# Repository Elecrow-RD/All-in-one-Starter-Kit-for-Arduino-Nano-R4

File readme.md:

## Menu
### 1, Product picture
### 2, Product version number
### 3, product information
### 4, Use the driver module
### 5,Quick Start
### 6,Folder structure.
### 7,Pin definition

### 1, Product picture

#### 2, Product version number

|      | Hardware | Software | Remark |
| ---- | -------- | -------- | ------ |
| 1    | V1.0     | V1.0     | latest |

### 3, product information

| Main Processor        | Arduino NANO R4                                        |
| --------------------- | ------------------------------------------------------ |
| CPU/SoC               | RA4M1(Arm® Cortex-M4®)                                 |
| System memory         | RAM32KB                                                |
| Storage               | Flash 256 kB                                           |
| Bluetooth             | None                                                   |
| WiFi                  | None                                                   |
| Interface             | TYPE-C interface, I/O pins/sockets, Crowtail interface |
| Button                | Reset                                                  |
| LED indicator light   | Reset indicator light, power indicator light           |
| Power input           | 5V input charging                                      |
| Shell material        | PP (non-toxic)                                         |
| Size                  | 195\*170*46（mm）                                      |
| Net Weight            | 415g                                                      |
| Operating temperature | 0°C to 60°C                                            |
| Storage temperature   | 0°C to 60°C                                            |

### 4, Use the driver module

| Name     | dependency library                           |
| -------- | -------------------------------------------- |
| IRremote | Arduino-IRremote-master <br />version: 4.5.0 |
| LSM6DS3  | Arduino_LSM6DS3-master<br />version=1.0.3    |
| BH1750   | BH1750<br />version: 1.3.0                   |

### 5,Quick Start
### Arduino IDE starts

1.Download the library files used by this product to the 'libraries' folder.

C:\Users\Documents\Arduino\libraries\

2.Install the NANO R4 development board and open the program files

3.Open the code configuration environment and burn it

### 6,Folder structure.

|--Eagle_SCH&PCB: Contains **Eagle CAD** schematic (`.sch`) and PCB layout (`.brd`) files. These are used for circuit design and PCB manufacturing.

|--lesson_code: Provides  code and projects to demonstrate how to use the hardware and libraries. These examples help users get started quickly.

|--libraries: Includes necessary libraries required for compiling and running the project. These libraries provide drivers and additional functionalities for the hardware.

### 7,Pin definition

#### Sensor / Module List

| No.  | Sensor / Module Name          | Quantity | Notes                            | nano pin                                                     |
| ---- | ----------------------------- | -------- | -------------------------------- | ------------------------------------------------------------ |
| 1    | Temperature & Humidity Sensor | 1        |                                  | A4/SDA<br />A5/SCL<br />I2C  ADDRESS:0X38                    |
| 2    | Button                        | 3        |                                  | A3_KEY                                                       |
| 3    | Ultrasonic Ranging Sensor     | 1        |                                  | D7_US_ECHO<br />D6_US_TRIG                                   |
| 4    | Light Sensor                  | 1        |                                  | A4/SDA<br />A5/SCL<br />I2C  ADDRESS:0X5C                    |
| 5    | Linear Potentiometer          | 1        |                                  | A0_ROTARY                                                    |
| 6    | LED (Red + Yellow + Green)    | 3        | Red + Yellow + Green             | ~D5_LED_R<br />~D10_LED_Y<br />~D11_LED_G                    |
| 7    | Buzzer                        | 1        |                                  | D3_BUZZER                                                    |
| 8    | LCD Display                   | 1        |                                  | A4/SDA<br />A5/SCL<br />I2C  ADDRESS:0X27                    |
| 9    | Infrared Remote               | 1        | Includes remote controller       | D2_IR_R                                                      |
| 10   | Relay Module                  | 1        |                                  | D4_RELAY                                                     |
| 11   | Servo Motor                   | 1        |                                  | D9_SERVO                                                     |
| 12   | Sound Sensor                  | 1        |                                  | A1_SOUND                                                     |
| 13   | 3-Axis Accelerometer          | 1        |                                  | A4/SDA<br />A5/SCL<br />I2C  ADDRESS:0x6B (pin SDO is logic High) |
| 14   | PIR Motion Sensor             | 1        |                                  | A2_PIR                                                       |
| 15   | Soil Moisture Sensor          | 1        | Separate probe, 4-wire connector | A7                                                           |
| 16   | 4-Digit Display               | 1        |                                  | A4/SDA<br />A5/SCL<br />I2C  ADDRESS:0X70                    |

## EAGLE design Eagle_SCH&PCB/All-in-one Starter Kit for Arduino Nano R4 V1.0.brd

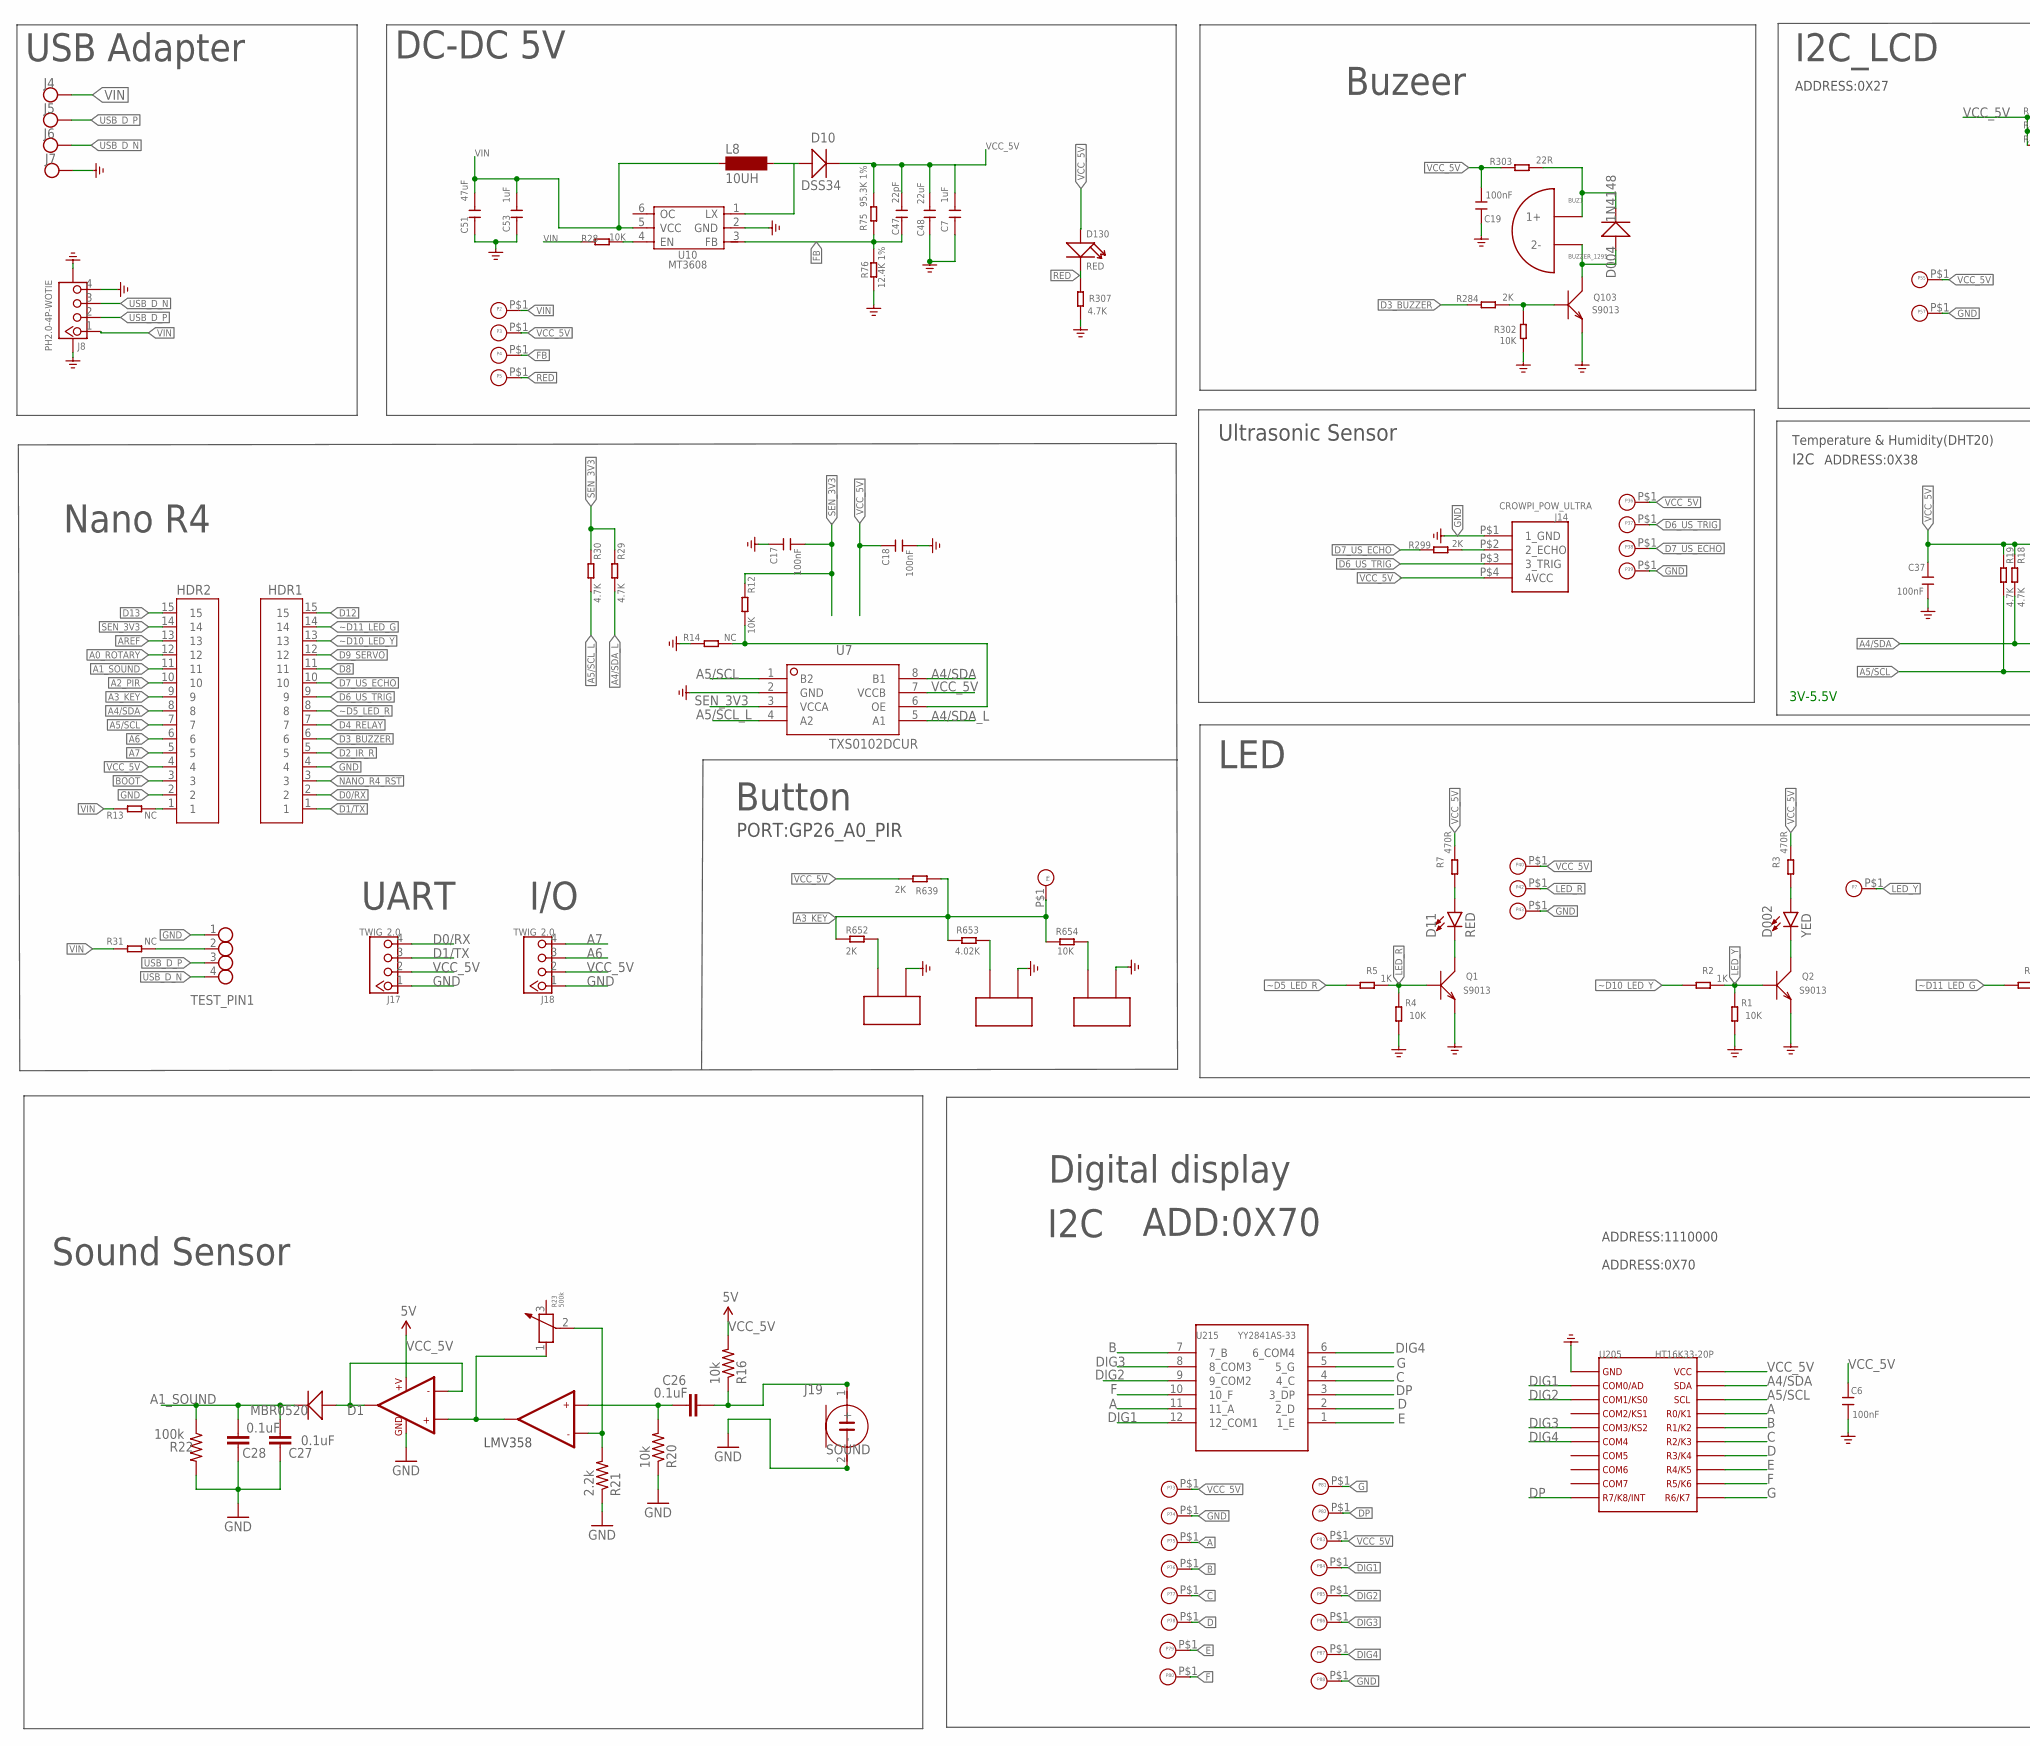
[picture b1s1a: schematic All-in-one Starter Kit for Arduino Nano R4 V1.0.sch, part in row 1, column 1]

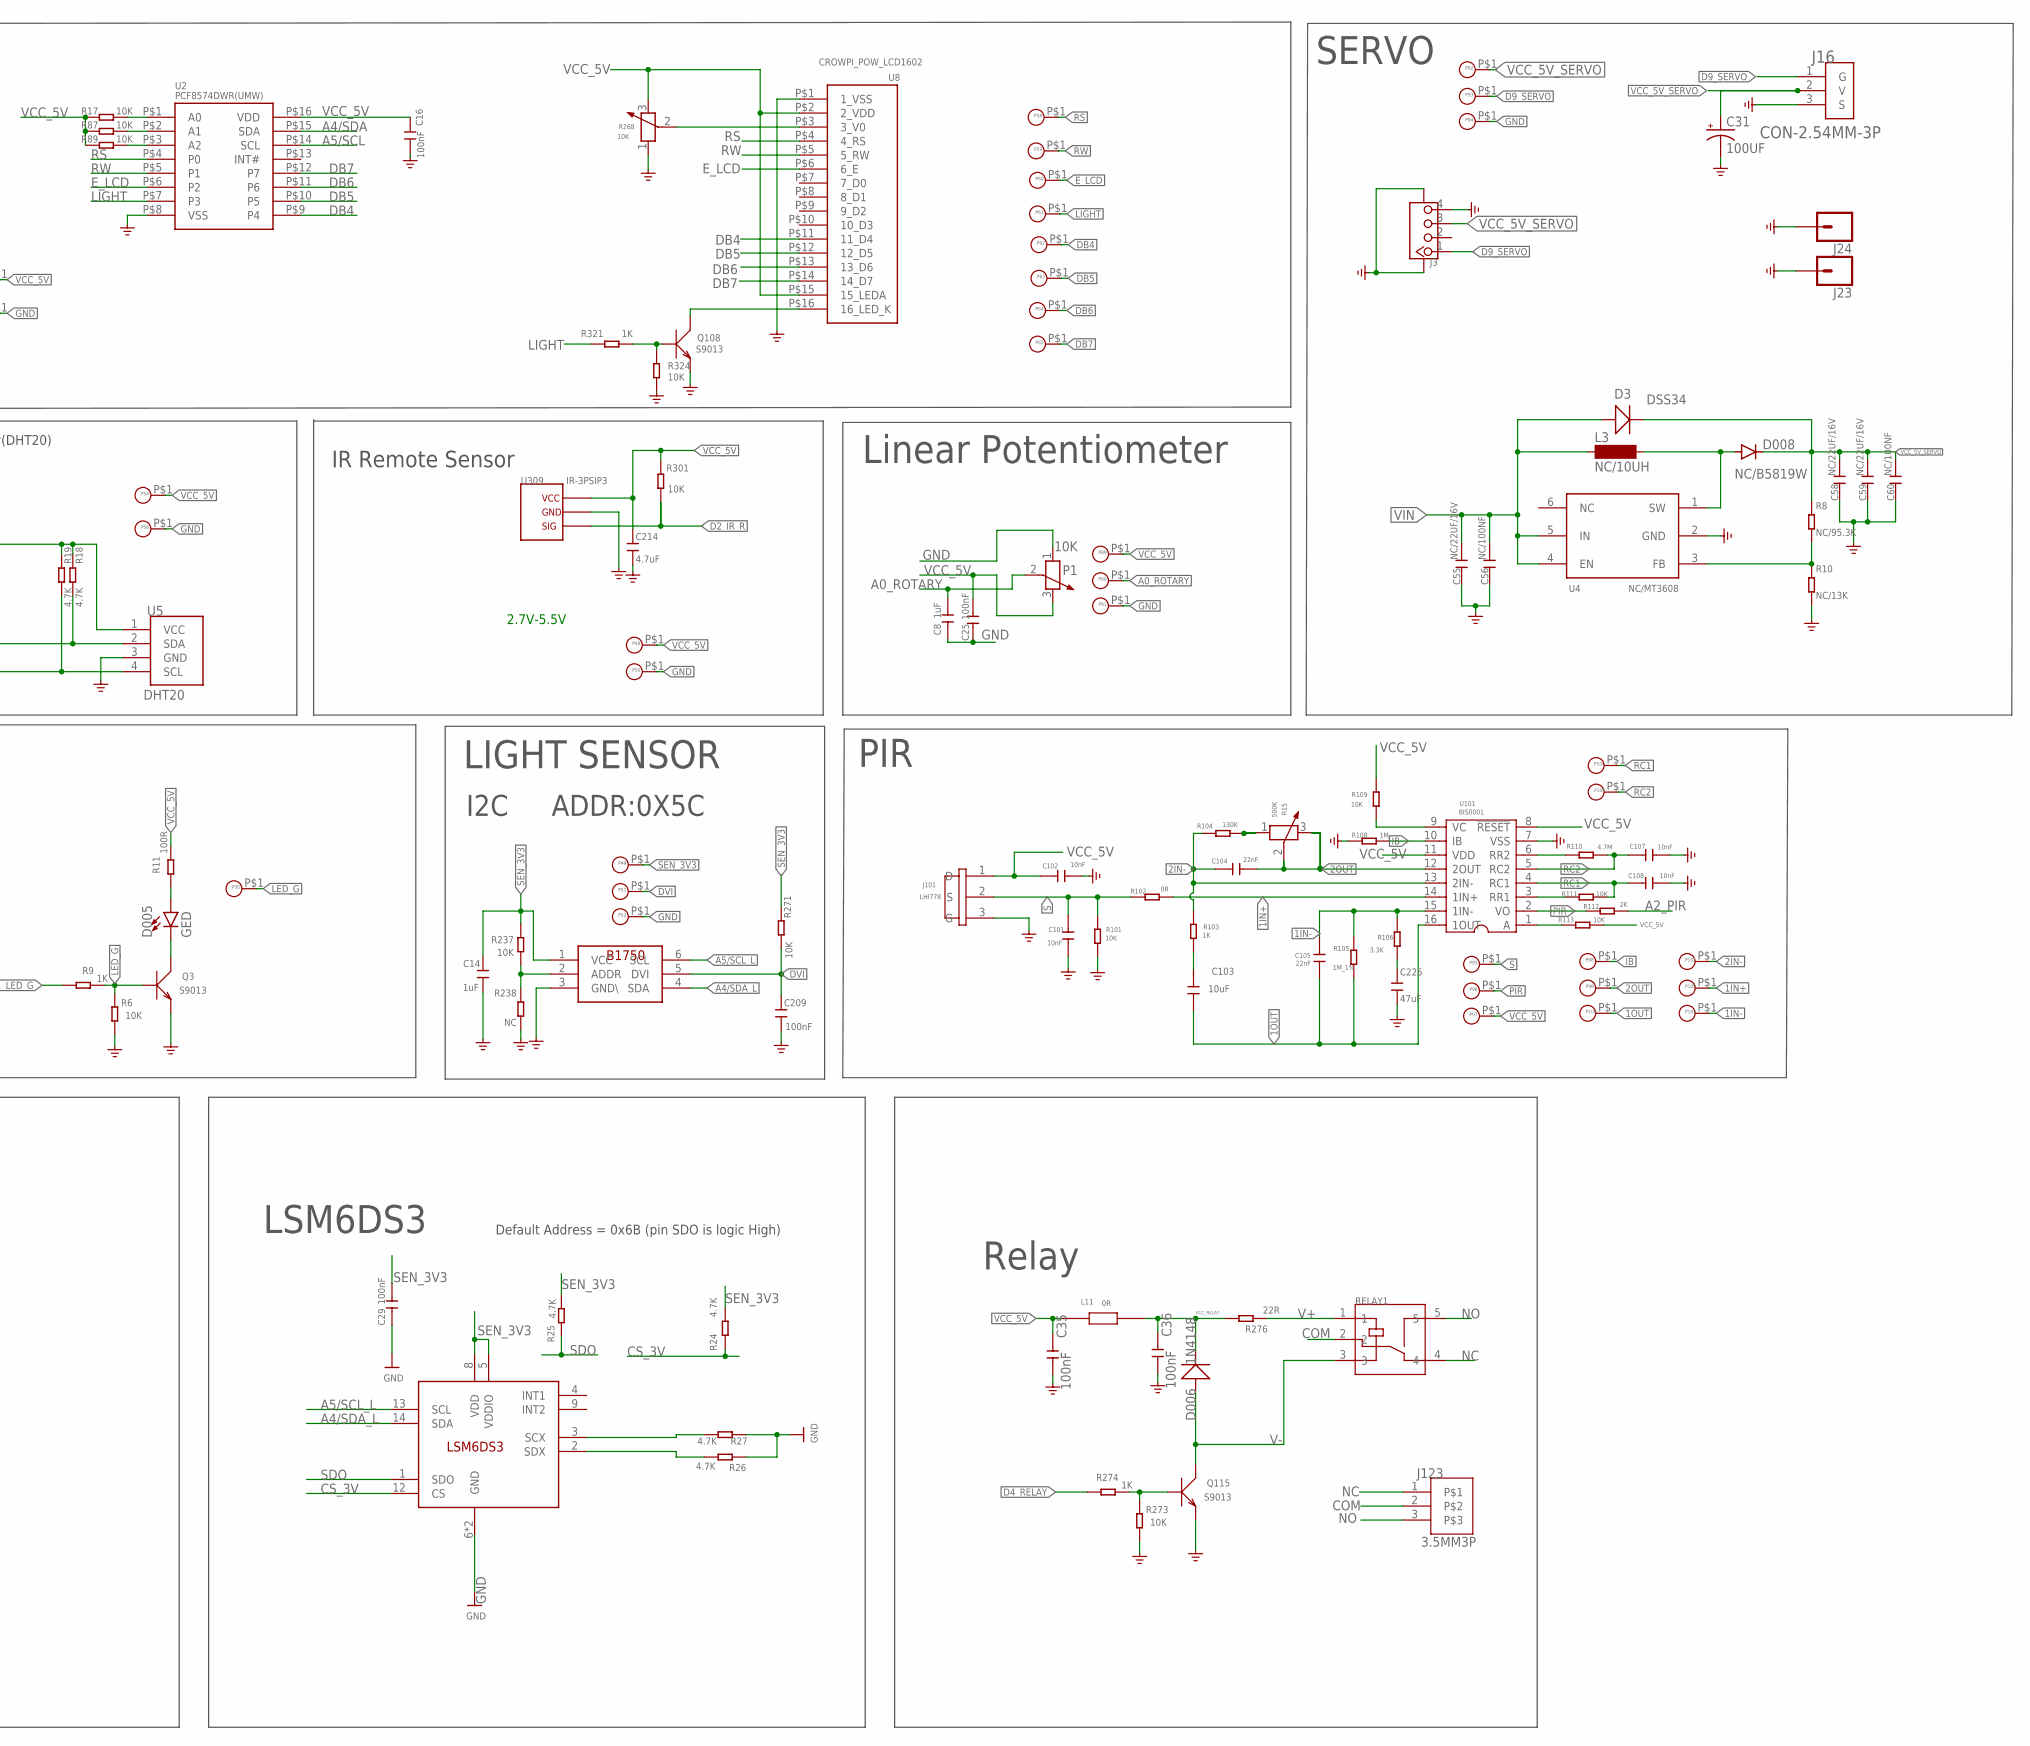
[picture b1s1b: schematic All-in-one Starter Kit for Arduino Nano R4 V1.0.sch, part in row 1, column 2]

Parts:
BUZ1: BUZZER_1295; BUZZER-D12MM-DIP2
C6, C16, C17, C18, C19, C37, C209: 100nF; 0603
C7, C8, C53: 1uF; C0603
C14: 1uF; 0603
C25, C29, C35, C36: 100nF; C0603
C26, C27, C28: 0.1uF; 0603-CAP
C31: 100UF; SANYO-OSCON_SMD_C6
C47: 22pF; C0603
C48: 22uF; C0805
C51: 47uF; C0805
C55, C58, C59: NC/22UF/16V; C0603
C56, C60: NC/100NF; C0603
C101, C102, C107, C108: 10nF; C0603
C103: 10uF; 0603
C104, C105: 22nF; C0603
C214: 4.7uF; 0603
C225: 47uF; 0805
D1: MBR0520; SOD123-2.7X1.6
D002: YED; LED-8MM
D3, D10: DSS34; D_SOD123FL
D004, D006: 1N4148; D_SOD123
D005: GED; LED-8MM
D008: NC/B5819W; SOD-123_MINI-SMA
D11: RED; LED-8MM
D130: RED; LED_0603_SMT
HDR1, HDR2: KH-2.54FH-1X15P-H8.5; HDR-TH_15P-P2.54-V-F
J3: A_XBJ_CONNECTOR_TWIG-4P-2.0-SMD-FEMALE-REINFORCE9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; A_XBJ_CONNECTOR_4P-SMD-2.0-90D
J4, J5, J6, J7: TP-SMDTP-SMD-2X4MM; TP-SMD-2X4MM
J8: PH2.0-4P-WOTIE; PH2.0-4P
J14: CROWPI_POW_ULTRA
J16: CON-2.54MM-3P; CON-PZ-2.54MM-1*3P-WT
J17, J18: TWIG_2.0; 2.0_1X4
J19: SOUND; TEMPLATE_2P-D8.9MM
J23, J24: CONN_01_2.6MM1X01_2.6-4MM; 1X01_2.6MM
J101: LHI778; 3P-D8.1MM
J123: 3.5MM3P; 3.5MM*3P
K1, K2, K3: BUTTON_2P
L3: NC/10UH; MS42
L8: 10UH; MS42
L11: 0R; 201209
P1: 10K; 3P-SQUA-45.6X10X5.8H
P2, P3, P4, P5, P6, P7, P30, P36, P37, P38, P39, P40, P42, P43, P48, P49, P50, P51, P52, P54, P55, P56, P57, P58, P59, P60, P61, P62, P63, P64, P65, P73, P74, P75, P76, P77, P78, P79, P80, P81, P82, P83, P84, P85, P86, P87, P88, P89, P90, P91, P92, P93, P94, P95, P96, P97, P98, P99, P100, P101, P102, P103, P104, P105: PADPAD-1.0MM; PAD-1.0MM
Q1, Q2, Q3, Q103, Q108, Q115: S9013; SOT23@1
R1, R4, R6, R12, R17, R87, R89, R101, R109, R111, R113, R237, R271, R273, R301, R302, R324, R654: 10K; R0603
R2, R5, R9, R103, R274, R321: 1K; R0603
R3, R7: 470R; R0603
R8: NC/95.3K; R0603
R10: NC/13K; R0603
R11: 100R; R0603
R13, R14, R31, R238: NC; R0603
R15: 500K; 3P-SMD-SQUA-3.6X3.3
R16, R20: 10k; 0603-RES
R18, R19, R24, R25, R26, R27, R29, R30, R307: 4.7K; R0603
R21: 2.2k; 0603-RES
R22: 100k; 0603-RES
R23: 500k; 3P-SMD-SQUA-3.6X3.3
R28: 10K; R0603-SP
R75: 95.3K 1%; R0603-SP
R76: 12.4K 1%; R0603-SP
R102: 0R; R0603
R104: 130K; R0603
R105: 1M_1%; R0603
R106: 3.3K; R0603
R108: 1M; R0603
R110: 4.7M; R0603
R112, R284, R299, R639, R652: 2K; R0603
R268: 10K; 3P-SMD-SQUA-3.6X3.3
R276, R303: 22R; R0603
R653: 4.02K; R0603
RELAY1: RELAY-SRD; REY5-6-19.1X15.5X15.3MM
TEST_PIN1: POGOPIN_4
U1: BH1750; BH1750-WSOF-6
U2: PCF8574DWR(UMW); SO-16-300MIL
U3: LSM6DS3; LGA-14L
U4: NC/MT3608; DBV_R-PDSO-G6
U5: DHT20; CROWTAIL-DHT20-V1.0-20211013_DHT20
U6: LMV358; SO08
U7: TXS0102DCUR; VSSOP-8
U8: CROWPI_POW_LCD1602; CROWPI_POW_LCD1206
U10: MT3608; SOT23-6L
U101: BIS0001; SOP16
U205: HT16K33-20P; HT16K33-SOP20
U215: YY2841AS-33; 4-DIGITAL_DISPLAY
U309: IR-3PSIP3; VS1838B-SIP3

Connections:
1IN+: P102.P$1, R102.1, U101.14 (1IN+)
1IN-: C105.2, P103.P$1, R105.2, R106.2, U101.15 (1IN-)
1OUT: C103.2, C105.1, P100.P$1, R105.1, U101.16 (1OUT)
2IN-: C104.1, P101.P$1, R103.2, R104.2, U101.13 (2IN-)
2OUT: C104.2, P99.P$1, R15.2 (3), R15.3 (2), U101.12 (2OUT)
A: P75.P$1, U205.P$17, U215.11 (11_A)
A0_ROTARY: C8.2, HDR2.12, P1.2 (3), P90.P$1
A1_SOUND: C27.2, C28.2, D1.2 (-), HDR2.11, R22.1
A2_PIR: HDR2.10, R112.1
A3_KEY: HDR2.9, P6.P$1, R639.2, R652.2, R653.2, R654.2
A4/SDA: HDR2.8, R18.2, U2.P$15 (SDA), U5.2 (SDA), U7.8 (B1), U205.P$19
A4/SDA_L: R29.2, U1.4 (SDA), U3.14 (SDA), U7.5 (A1)
A5/SCL: HDR2.7, R19.2, U2.P$14 (SCL), U5.4 (SCL), U7.1 (B2), U205.P$18
A5/SCL_L: R30.2, U1.6 (SCL), U3.13 (SCL), U7.4 (A2)
A6: HDR2.6, J18.3
A7: HDR2.5, J18.4
AREF: HDR2.13
B: P76.P$1, U205.P$16, U215.7 (7_B)
BOOT: HDR2.3
C: P77.P$1, U205.P$15, U215.4 (4_C)
COM: J123.2, RELAY1.2
CS_3V: R24.1, U3.12 (CS)
D: P78.P$1, U205.P$14, U215.2 (2_D)
D0/RX: HDR1.2, J17.4
D1/TX: HDR1.1, J17.3
D2_IR_R: HDR1.5, R301.2, U309.3
D3_BUZZER: HDR1.6, R284.1
D4_RELAY: HDR1.7, R274.2
D6_US_TRIG: HDR1.9, J14.P$3 (3_TRIG), P37.P$1
D7_US_ECHO: HDR1.10, P38.P$1, R299.2
D8: HDR1.11
D9_SERVO: HDR1.12, J3.1, J16.1 (G), P93.P$1
D12: HDR1.15
D13: HDR2.15
DB4: P62.P$1, U2.P$9 (P4), U8.P$11 (11_D4)
DB5: P63.P$1, U2.P$10 (P5), U8.P$12 (12_D5)
DB6: P64.P$1, U2.P$11 (P6), U8.P$13 (13_D6)
DB7: P65.P$1, U2.P$12 (P7), U8.P$14 (14_D7)
DIG1: P84.P$1, U205.P$2, U215.12 (12_COM1)
DIG2: P85.P$1, U205.P$3, U215.9 (9_COM2)
DIG3: P86.P$1, U205.P$5, U215.8 (8_COM3)
DIG4: P87.P$1, U205.P$6, U215.6 (6_COM4)
DP: P82.P$1, U205.P$10, U215.3 (3_DP)
DVI: C209.2, P51.P$1, R271.2, U1.5 (DVI)
E: P79.P$1, U205.P$13, U215.1 (1_E)
E_LCD: P60.P$1, U2.P$6 (P2), U8.P$6 (6_E)
F: P80.P$1, U205.P$12, U215.10 (10_F)
FB: C47.2, P4.P$1, R75.1, R76.2, U10.3 (FB)
G: P81.P$1, U205.P$11, U215.5 (5_G)
GND: C6.1, C7.1, C8.1, C14.1, C16.1, C17.2, C18.1, C19.2, C25.1, C27.1, C28.1, C29.1, C31.-, C35.1, C36.1, C37.1, C48.1, C51.1, C53.1, C55.1, C56.1, C58.1, C59.1, C60.1, C101.1, C102.1, C107.2, C108.2, C209.1, C214.1, C225.1, HDR1.4, HDR2.2, J3.4, J3.SS1, J3.SS2, J7.1, J8.4, J8.5 (SS1), J8.6 (SS2), J14.P$1 (1_GND), J16.3 (S), J17.1, J18.1, J19.2 (-), J23.1, J24.1, J101.3 (G), K1.P$1, K2.P$1, K3.P$1, P1.1, P39.P$1, P43.P$1, P50.P$1, P52.P$1, P56.P$1, P57.P$1, P74.P$1, P88.P$1, P91.P$1, P94.P$1, Q1.2 (E), Q2.2 (E), Q3.2 (E), Q103.2 (E), Q108.2 (E), Q115.2 (E), R1.1, R4.1, R6.1, R10.2, R14.1, R20.1, R21.1, R22.2, R26.1, R27.1, R76.1, R101.1, R108.1, R238.1, R268.1, R273.1, R302.1, R307.2, R324.2, TEST_PIN1.1, U1.3 (GND\), U2.P$8 (VSS), U3.6 (GND), U3.7 (GND), U4.2 (GND), U5.3 (GND), U6.4 (GND), U7.2 (GND), U8.P$1 (1_VSS), U10.2 (GND), U101.7 (VSS), U205.P$1, U309.2
IB: P98.P$1, R108.2, U101.10 (IB)
LED_G: P30.P$1, Q3.1 (B), R6.2, R9.1
LED_R: P42.P$1, Q1.1 (B), R4.2, R5.1
LED_Y: P7.P$1, Q2.1 (B), R1.2, R2.1
LIGHT: P61.P$1, R321.2, U2.P$7 (P3)
unnamed: R111.1, U101.3 (RR1)
unnamed: Q108.1 (B), R321.1, R324.1
unnamed: C225.2, R106.1
unnamed: D10.+, L8.2, U10.1 (LX)
unnamed: D002.2 (C), Q2.3 (C)
unnamed: R28.2, U10.4 (EN)
unnamed: R268.2 (3), U8.P$3 (3_V0)
unnamed: D002.1 (A), R3.2
unnamed: D005.2 (C), Q3.3 (C)
unnamed: R17.2, U2.P$1 (A0)
unnamed: R87.2, U2.P$2 (A1)
unnamed: R89.2, U2.P$3 (A2)
unnamed: D008.A, L3.2, U4.1 (SW)
unnamed: D005.1 (A), R11.2
unnamed: D11.2 (C), Q1.3 (C)
unnamed: D11.1 (A), R7.2
unnamed: R31.1, TEST_PIN1.2
unnamed: HDR2.1, R13.1
unnamed: Q108.3 (C), U8.P$16 (16_LED_K)
unnamed: R12.2, R14.2, U7.6 (OE)
unnamed: R110.2, U101.6 (RR2)
unnamed: R109.2, U101.9 (VC)
unnamed: C103.1, R103.1
unnamed: R8.2, R10.1, U4.3 (FB)
unnamed: R113.2, U101.1 (A)
unnamed: R15.1, R104.1
unnamed: C26.1, J19.1 (+), R16.1
unnamed: C26.2, R20.2, U6.5 (+IN2)
unnamed: R21.2, R23.2 (3), U6.6 (-IN2)
unnamed: D1.1 (+), U6.1 (OUT1), U6.2 (-IN1)
unnamed: R23.1, U6.3 (+IN1), U6.7 (OUT2)
unnamed: R26.2, U3.2 (SDX)
unnamed: R27.2, U3.3 (SCX)
unnamed: K1.P$2, R652.1
unnamed: K2.P$2, R653.1
unnamed: K3.P$2, R654.1
unnamed: R237.1, R238.2, U1.2 (ADDR)
unnamed: Q115.1 (B), R273.2, R274.1
unnamed: J14.P$2 (2_ECHO), R299.1
unnamed: Q103.1 (B), R284.2, R302.2
unnamed: BUZ1.2 (2-), D004.+, Q103.3 (C)
unnamed: BUZ1.1 (1+), D004.-, R303.2
NANO_R4_RST: HDR1.3
NC: J123.1, RELAY1.4
NO: J123.3, RELAY1.5
PIR: P96.P$1, R112.2, U101.2 (VO)
RC1: C108.1, P104.P$1, R111.2, U101.4 (RC1)
RC2: C107.1, P105.P$1, R110.1, U101.5 (RC2)
RED: D130.2 (2_K), P5.P$1, R307.1
RS: P58.P$1, U2.P$4 (P0), U8.P$4 (4_RS)
RW: P59.P$1, U2.P$5 (P1), U8.P$5 (5_RW)
S: C101.2, J101.2 (S), P95.P$1, R101.2, R102.2
SDO: R25.1, U3.1 (SDO)
SEN_3V3: C14.2, C17.1, C29.2, HDR2.14, P49.P$1, R12.1, R24.2, R25.2, R29.1, R30.1, R237.2, R271.1, U1.1 (VCC), U3.5 (VDDIO), U3.8 (VDD), U7.3 (VCCA)
USB_D_N: J6.1, J8.3, TEST_PIN1.4
USB_D_P: J5.1, J8.2, TEST_PIN1.3
V+: R276.2, RELAY1.1
V-: D006.+, Q115.3 (C), RELAY1.3
VCC_5V: C6.2, C7.2, C16.2, C18.2, C19.1, C25.2, C35.2, C37.2, C47.1, C48.2, C102.2, C214.2, D10.-, D130.1 (1_A), HDR2.4, J14.P$4 (4VCC), J17.2, J18.2, J101.1 (D), L11.1, P1.3 (2), P3.P$1, P36.P$1, P40.P$1, P48.P$1, P54.P$1, P55.P$1, P73.P$1, P83.P$1, P89.P$1, P97.P$1, R3.1, R7.1, R11.1, R16.2, R17.1, R18.1, R19.1, R75.2, R87.1, R89.1, R109.1, R113.1, R268.3 (2), R301.1, R303.1, R639.1, U2.P$16 (VDD), U5.1 (VCC), U6.8 (+V), U7.7 (VCCB), U8.P$2 (2_VDD), U8.P$15 (15_LEDA), U101.8 (!RESET), U101.11 (VDD), U205.P$20, U309.1
VCC_5V_SERVO: C31.+, C58.2, C59.2, C60.2, D3.-, D008.C, J3.3, J16.2 (V), P92.P$1, R8.1
VCC_RELAY: C36.2, D006.-, L11.2, R276.1
VIN: C51.2, C53.2, C55.2, C56.2, D3.+, J4.1, J8.1, L3.1, L8.1, P2.P$1, R13.2, R28.1, R31.2, U4.4 (EN), U4.5 (IN), U10.5 (VCC)
~D5_LED_R: HDR1.8, R5.2
~D10_LED_Y: HDR1.13, R2.2
~D11_LED_G: HDR1.14, R9.2

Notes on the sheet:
I2C_LCD
LIGHT SENSOR
SERVO
Ultrasonic Sensor
IR Remote Sensor
I2C
Temperature & Humidity(DHT20)
PIR
2.7V-5.5V
3V-5.5V
ADDRESS:0X38
ADDRESS:0X27
LED
Linear Potentiometer
DC-DC 5V
USB Adapter
ADDR:0X5C
Nano R4
Digital display
ADDRESS:0X70
ADDRESS:1110000
ADD:0X70
UART
I/O
Buzeer
Default Address = 0x6B (pin SDO is logic High)
LSM6DS3
Sound Sensor
LMV358
Relay
Button
PORT:GP26_A0_PIR

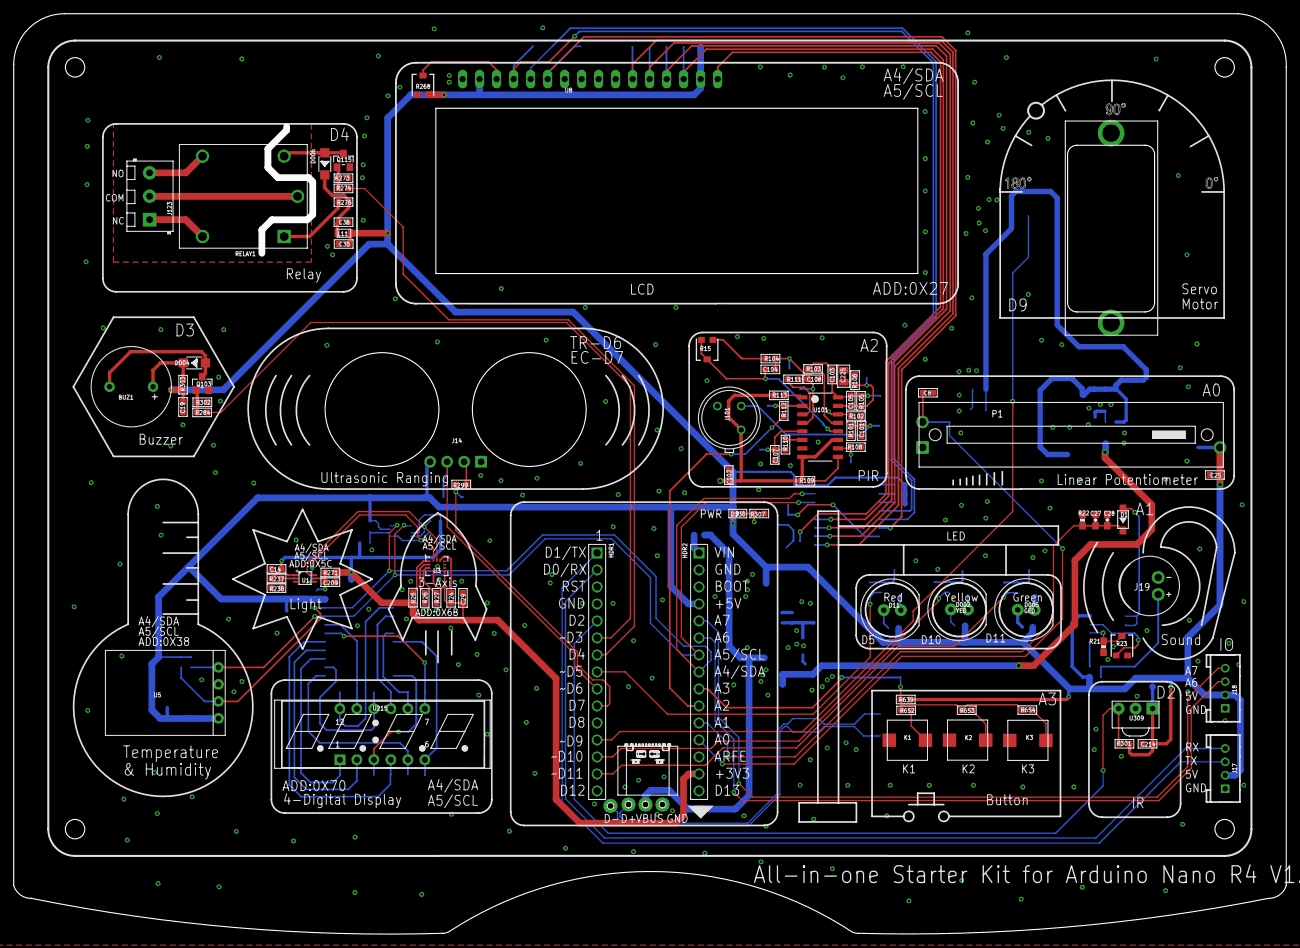
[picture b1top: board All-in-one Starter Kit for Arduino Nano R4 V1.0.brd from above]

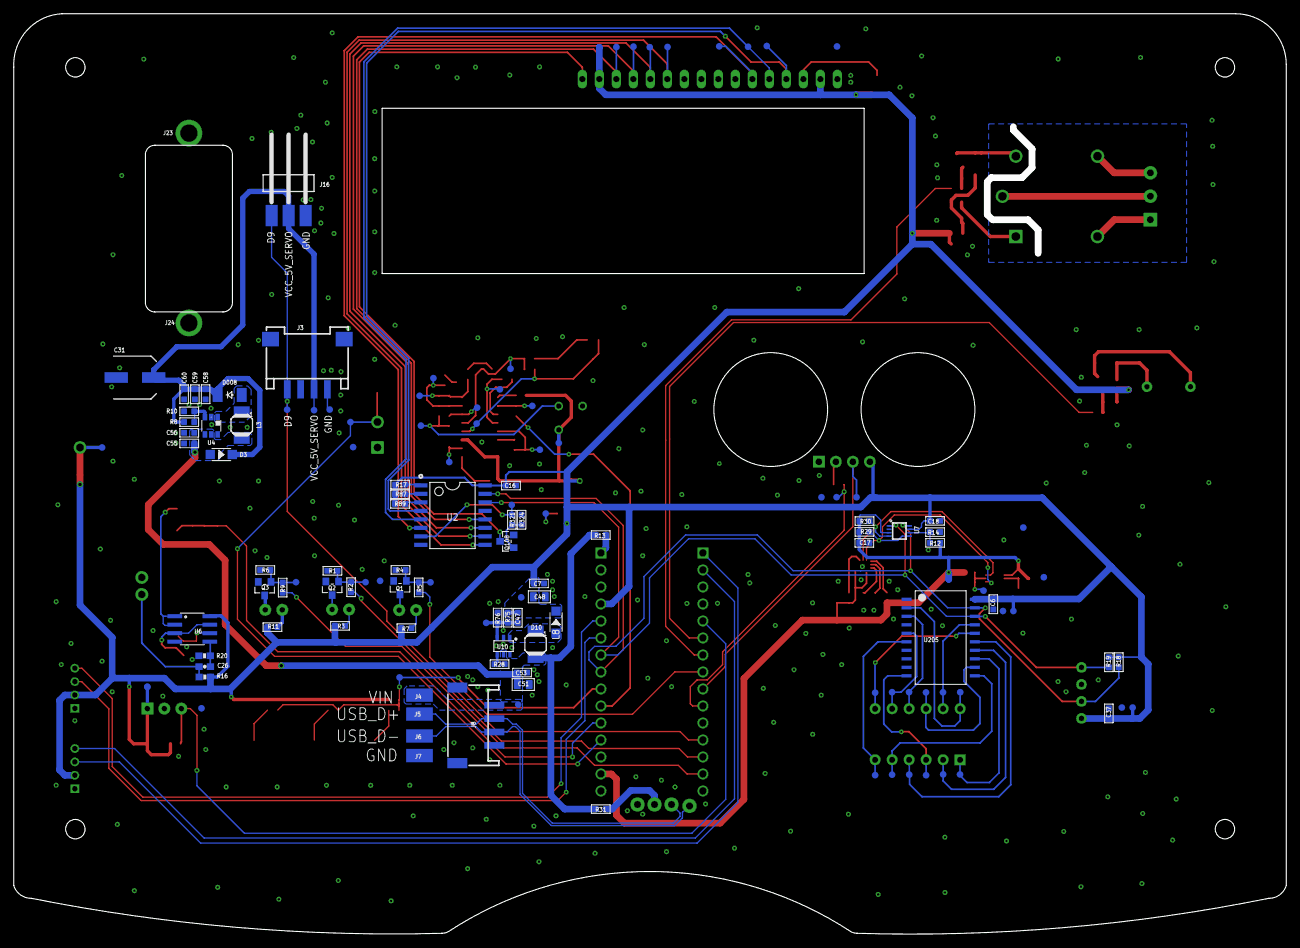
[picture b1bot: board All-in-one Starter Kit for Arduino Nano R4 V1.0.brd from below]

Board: 2 copper layers, 190.1 x 137.5 mm, 222 parts (134 on the bottom side), 114 nets.

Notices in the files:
parts and their libraries:
SparkFun-Connectors2.6: Licensing: Creative Commons ShareAlike 4.0 International - https://creativecommons.org/licenses/by-sa/4.0
microbuilder: This work is placed in the public domain, and may be freely used for commercial and non-commercial work with the following conditions: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
